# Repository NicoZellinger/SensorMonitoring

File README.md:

#Universal Data Aquisition Network System

#SensorMonitoring
In this project a system should be developed which is possible to carry out several sensor measurements and to send the values over WLAN to a central system. 
Afterwards in the central system the measuring results should be evaluated and documented for a period. 

# Hardware
In the essentials the sensor board is a WLAN module, a microcontroller and any sensor. 
The microcontroller reads the values of the sensor in a configureable frequency and transfers this to the WLAN module. 
The WLAN module sends the values to the central system (Raspberry Pi with Raspbian). 
Afterwards on the central system the measuring results are evaluated and documented. 
Beyond it, the central system administered the sensor boards. 

# Power
So that the sensor boards can be used mobile, the boards are supplied with a 3 volt battery. 
To put off the unloading of the battery as long as possible a "ultra low power" microcontroller from STMicroelectronic is used.
Besides, the controller is moved, as long as he takes up no measurement, into the Sleep mode. 
Above, the WLAN module and the sensor is separated with the help of a FET from the supply voltage (As long as no measurement is made).

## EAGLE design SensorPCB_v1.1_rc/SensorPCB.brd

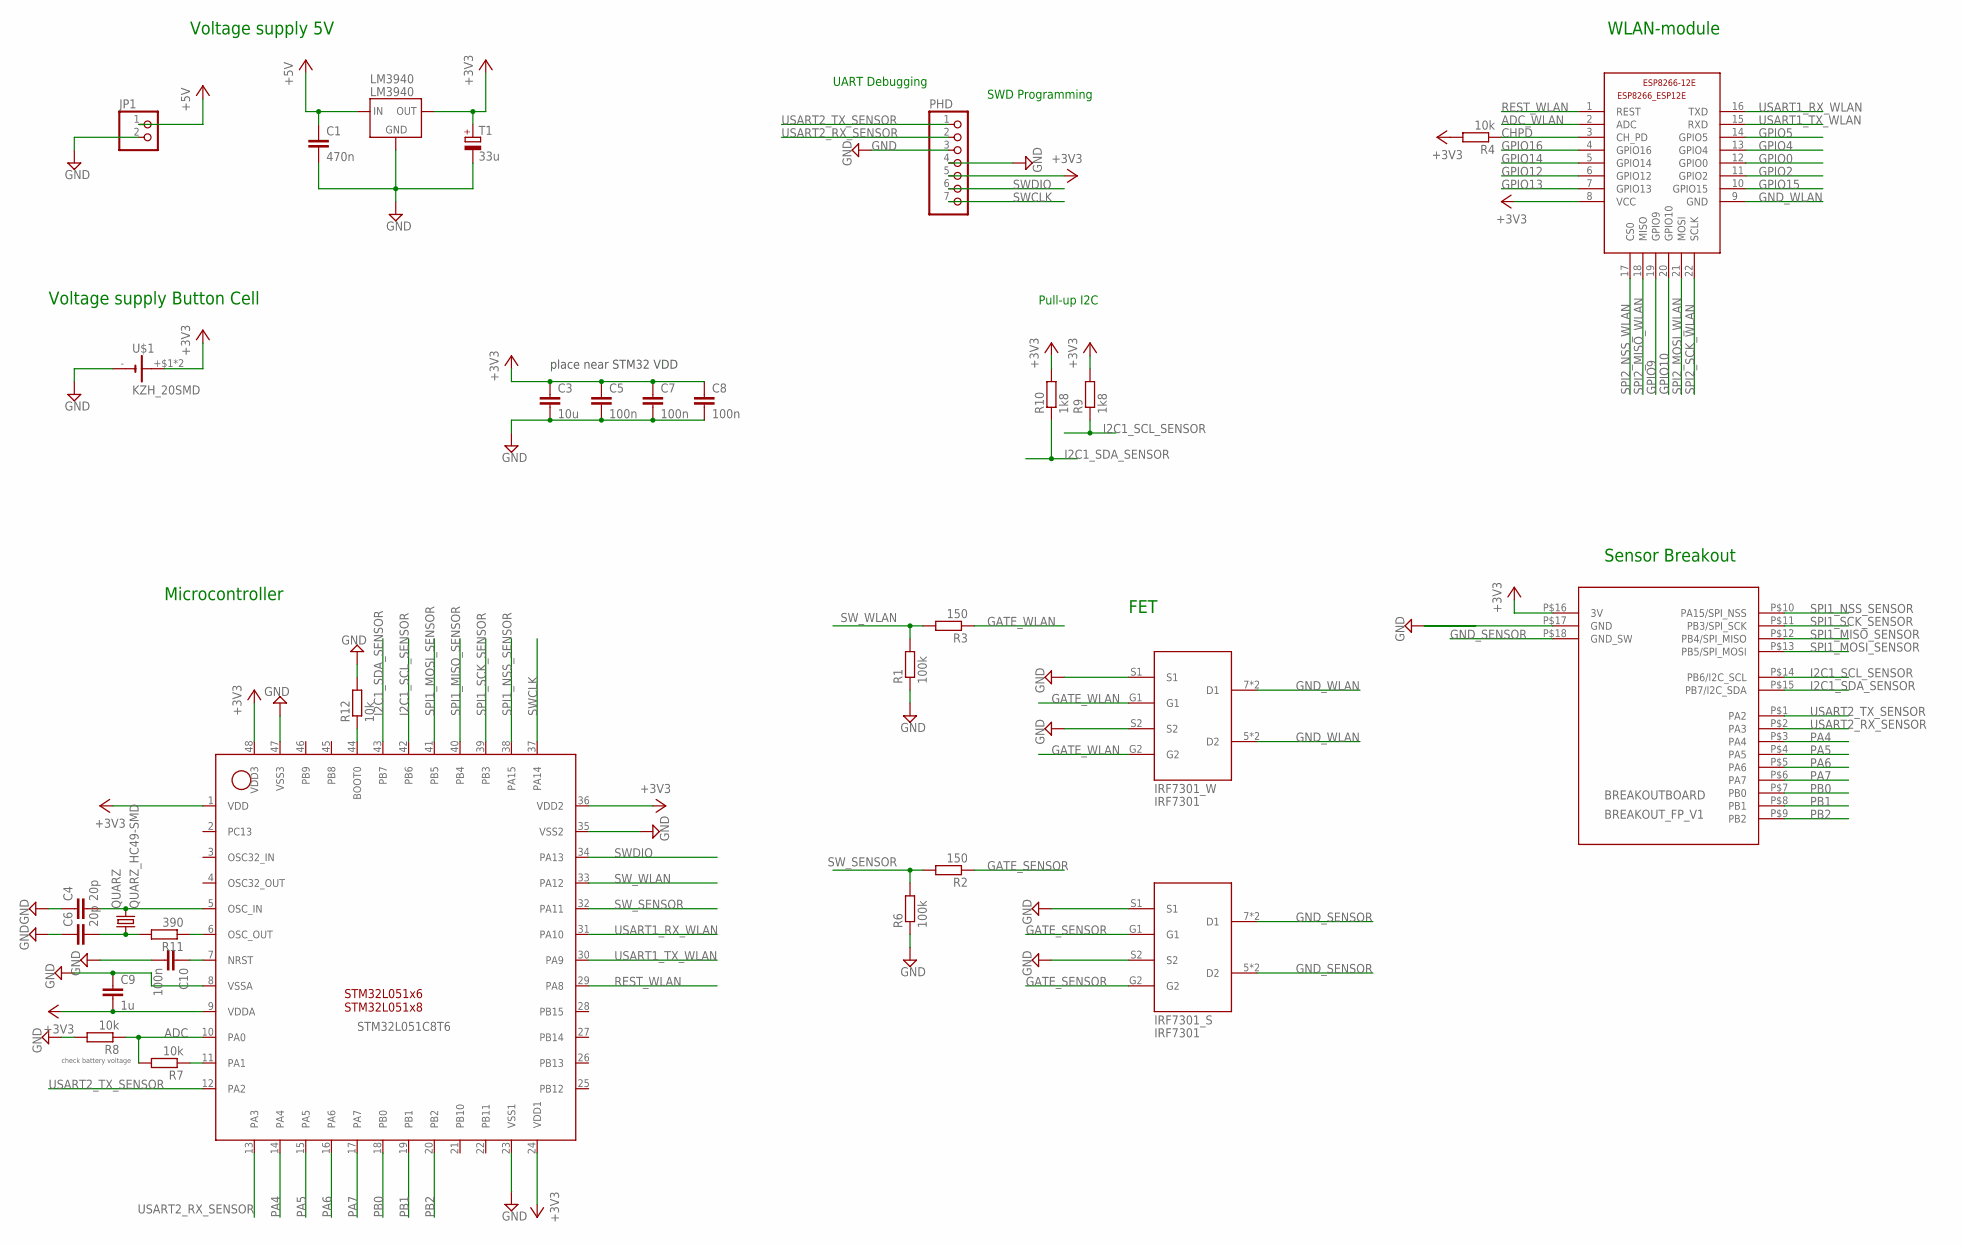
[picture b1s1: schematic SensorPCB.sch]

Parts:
BREAKOUTBOARD: BREAKOUT_FP_V1; BREAKOUT_FOOTPRINT_V1
C1: 470n; C0805
C3: 10u; C0805
C4, C6: 20p; C0805
C5, C7, C8, C10: 100n; C0805
C9: 1u; C0805
ESP8266-12E: ESP8266-12EESP8266-ESP12E; ESP8266-ESP12E
IRF7301_S, IRF7301_W: IRF7301; IRF7301_PACK_SO8
JP1: PINHD-1X2_2.54-SMD; 1X02SMD
LM3940: LM3940; LM3940_PACK
PHD: PINHD-1X7_2.54-SMD; 1X07SMD
QUARZ: QUARZ_HC49-SMD; HC49-SMD
R1, R6: 100k; R0805
R2, R3: 150; R0805
R4, R7, R8, R12: 10k; R0805
R9, R10: 1k8; R0805
R11: 390; R0805
STM32L051C8T6: STM32L051X6/8; LQFP48
T1: 33u; 1206
U$1: KZH_20SMD; KHZ_20SMD

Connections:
+3V3: BREAKOUTBOARD.P$16 (3V), C3.1, C5.1, C7.1, C8.1, C9.2, ESP8266-12E.8 (VCC), LM3940.3 (OUT), PHD.5, R4.2, R9.2, R10.2, STM32L051C8T6.1 (VDD), STM32L051C8T6.9 (VDDA), STM32L051C8T6.24 (VDD1), STM32L051C8T6.36 (VDD2), STM32L051C8T6.48 (VDD3), T1.1 (+), U$1.+$1 (+), U$1.+$2 (+)
+5V: C1.1, JP1.1, LM3940.1 (IN)
ADC: R7.2, R8.1, STM32L051C8T6.10 (PA0)
ADC_WLAN: ESP8266-12E.2 (ADC)
CHPD: ESP8266-12E.3 (CH_PD), R4.1
GATE_SENSOR: IRF7301_S.G1, IRF7301_S.G2, R2.1
GATE_WLAN: IRF7301_W.G1, IRF7301_W.G2, R3.1
GND: BREAKOUTBOARD.P$17 (GND), C1.2, C3.2, C4.1, C5.2, C6.1, C7.2, C8.2, C9.1, C10.2, IRF7301_S.S1, IRF7301_S.S2, IRF7301_W.S1, IRF7301_W.S2, JP1.2, LM3940.2 (GND), LM3940.4 (GND), PHD.3, PHD.4, R1.1, R6.1, R8.2, R12.2, STM32L051C8T6.8 (VSSA), STM32L051C8T6.23 (VSS1), STM32L051C8T6.35 (VSS2), STM32L051C8T6.47 (VSS3), T1.2 (-), U$1.-
GND_SENSOR: BREAKOUTBOARD.P$18 (GND_SW), IRF7301_S.5 (D2), IRF7301_S.7 (D1), IRF7301_S.D1, IRF7301_S.D2
GND_WLAN: ESP8266-12E.9 (GND), IRF7301_W.5 (D2), IRF7301_W.7 (D1), IRF7301_W.D1, IRF7301_W.D2
GPIO0: ESP8266-12E.12 (GPIO0)
GPIO2: ESP8266-12E.11 (GPIO2)
GPIO4: ESP8266-12E.13 (GPIO4)
GPIO5: ESP8266-12E.14 (GPIO5)
GPIO9: ESP8266-12E.19 (GPIO9)
GPIO10: ESP8266-12E.20 (GPIO10)
GPIO12: ESP8266-12E.6 (GPIO12)
GPIO13: ESP8266-12E.7 (GPIO13)
GPIO14: ESP8266-12E.5 (GPIO14)
GPIO15: ESP8266-12E.10 (GPIO15)
GPIO16: ESP8266-12E.4 (GPIO16)
I2C1_SCL_SENSOR: BREAKOUTBOARD.P$14 (PB6/I2C_SCL), R9.1, STM32L051C8T6.42 (PB6)
I2C1_SDA_SENSOR: BREAKOUTBOARD.P$15 (PB7/I2C_SDA), R10.1, STM32L051C8T6.43 (PB7)
unnamed: R7.1, STM32L051C8T6.11 (PA1)
unnamed: C6.2, QUARZ.1, R11.2
unnamed: C10.1, STM32L051C8T6.7 (NRST)
unnamed: R12.1, STM32L051C8T6.44 (BOOT0)
OSC_IN: C4.2, QUARZ.2, STM32L051C8T6.5 (OSC_IN)
OSC_OUT: R11.1, STM32L051C8T6.6 (OSC_OUT)
PA4: BREAKOUTBOARD.P$3 (PA4), STM32L051C8T6.14 (PA4)
PA5: BREAKOUTBOARD.P$4 (PA5), STM32L051C8T6.15 (PA5)
PA6: BREAKOUTBOARD.P$5 (PA6), STM32L051C8T6.16 (PA6)
PA7: BREAKOUTBOARD.P$6 (PA7), STM32L051C8T6.17 (PA7)
PB0: BREAKOUTBOARD.P$7 (PB0), STM32L051C8T6.18 (PB0)
PB1: BREAKOUTBOARD.P$8 (PB1), STM32L051C8T6.19 (PB1)
PB2: BREAKOUTBOARD.P$9 (PB2), STM32L051C8T6.20 (PB2)
REST_WLAN: ESP8266-12E.1 (REST), STM32L051C8T6.29 (PA8)
SPI1_MISO_SENSOR: BREAKOUTBOARD.P$12 (PB4/SPI_MISO), STM32L051C8T6.40 (PB4)
SPI1_MOSI_SENSOR: BREAKOUTBOARD.P$13 (PB5/SPI_MOSI), STM32L051C8T6.41 (PB5)
SPI1_NSS_SENSOR: BREAKOUTBOARD.P$10 (PA15/SPI_NSS), STM32L051C8T6.38 (PA15)
SPI1_SCK_SENSOR: BREAKOUTBOARD.P$11 (PB3/SPI_SCK), STM32L051C8T6.39 (PB3)
SPI2_MISO_WLAN: ESP8266-12E.18 (MISO)
SPI2_MOSI_WLAN: ESP8266-12E.21 (MOSI)
SPI2_NSS_WLAN: ESP8266-12E.17 (CS0)
SPI2_SCK_WLAN: ESP8266-12E.22 (SCLK)
SWCLK: PHD.7, STM32L051C8T6.37 (PA14)
SWDIO: PHD.6, STM32L051C8T6.34 (PA13)
SW_SENSOR: R2.2, R6.2, STM32L051C8T6.32 (PA11)
SW_WLAN: R1.2, R3.2, STM32L051C8T6.33 (PA12)
USART1_RX_WLAN: ESP8266-12E.16 (TXD), STM32L051C8T6.31 (PA10)
USART1_TX_WLAN: ESP8266-12E.15 (RXD), STM32L051C8T6.30 (PA9)
USART2_RX_SENSOR: BREAKOUTBOARD.P$2 (PA3), PHD.2, STM32L051C8T6.13 (PA3)
USART2_TX_SENSOR: BREAKOUTBOARD.P$1 (PA2), PHD.1, STM32L051C8T6.12 (PA2)

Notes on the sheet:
Voltage supply 5V
WLAN-module
Voltage supply Button Cell
Microcontroller
FET
Sensor Breakout
UART Debugging
SWD Programming
place near STM32 VDD
check battery voltage
Pull-up I2C

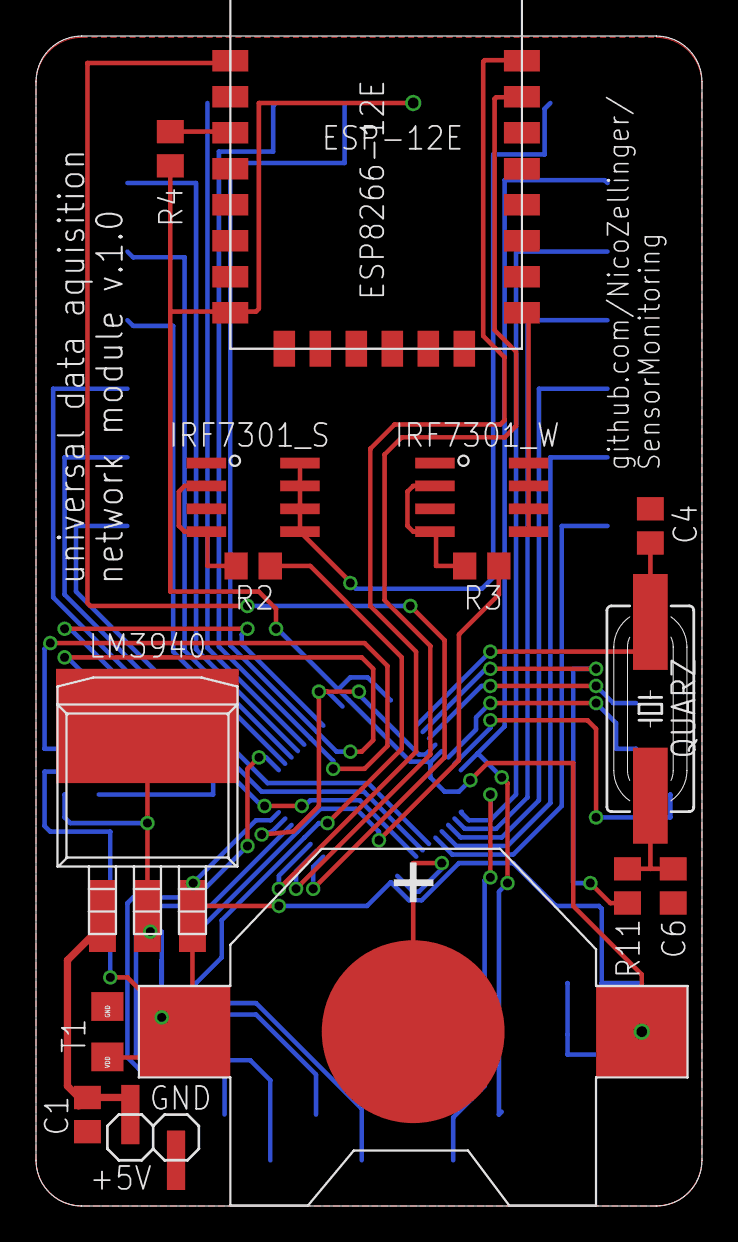
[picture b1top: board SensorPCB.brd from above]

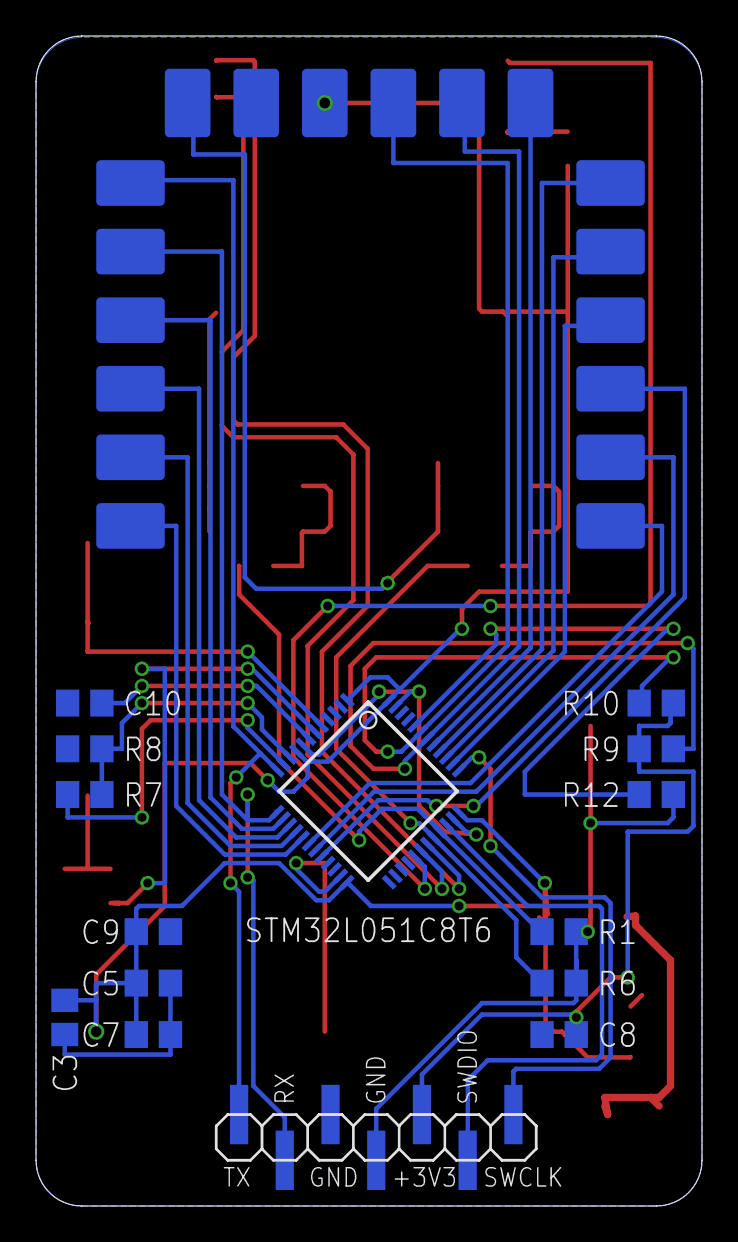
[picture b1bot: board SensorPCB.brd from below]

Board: 2 copper layers, 37.0 x 65.0 mm, 31 parts (16 on the bottom side), 37 nets.

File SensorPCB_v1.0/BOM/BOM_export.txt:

Partlist

Exported from SensorPCB.sch at 12.12.15 22:51

EAGLE Version 7.4.0 Copyright (c) 1988-2015 CadSoft

Assembly variant: 

Part          Value          Device                    Package               Library               Sheet

BREAKOUTBOARD BREAKOUT_FP_V1 BREAKOUT_FP_V1            BREAKOUT_FOOTPRINT_V1 breakout_base         1
C1            470n           C-EUC0805                 C0805                 rcl                   1
C3            10u            C-EUC0805                 C0805                 rcl                   1
C4            20p            C-EUC0805                 C0805                 rcl                   1
C5            100n           C-EUC0805                 C0805                 rcl                   1
C6            20p            C-EUC0805                 C0805                 rcl                   1
C7            100n           C-EUC0805                 C0805                 rcl                   1
C8            100n           C-EUC0805                 C0805                 rcl                   1
C9            1u             C-EUC0805                 C0805                 rcl                   1
C10           100n           C-EUC0805                 C0805                 rcl                   1
ESP8266-12E                  ESP8266-12EESP8266-ESP12E ESP8266-ESP12E        ESP8266-ESP12E        1
IRF7301_S     IRF7301        IRF7301                   IRF7301_PACK_SO8      irf7301_symb          1
IRF7301_W     IRF7301        IRF7301                   IRF7301_PACK_SO8      irf7301_symb          1
JP1                          PINHD-1X2_2.54-SMD        1X02SMD               pinhead               1
LM3940        LM3940         LM3940                    LM3940_PACK           lm3940                1
PHD                          PINHD-1X7_2.54-SMD        1X07SMD               pinhead               1
QUARZ         QUARZ_HC49-SMD QUARZ_HC49-SMD            HC49-SMD              quarz_hc49_smd        1
R1            100k           R-EU_R0805                R0805                 rcl                   1
R2            150            R-EU_R0805                R0805                 rcl                   1
R3            150            R-EU_R0805                R0805                 rcl                   1
R4            10k            R-EU_R0805                R0805                 rcl                   1
R6            100k           R-EU_R0805                R0805                 rcl                   1
R7            10k            R-EU_R0805                R0805                 rcl                   1
R8            10k            R-EU_R0805                R0805                 rcl                   1
R9            1k8            R-EU_R0805                R0805                 rcl                   1
R10           1k8            R-EU_R0805                R0805                 rcl                   1
R11           390            R-EU_R0805                R0805                 rcl                   1
R12           10k            R-EU_R0805                R0805                 rcl                   1
STM32L051C8T6 STM32L051X6/8  STM32L051X6/8             LQFP48                STM32L051x6_LQFP48XXL 1
T1            33u            CAP_TANTAL_1206           1206                  CAP_TANTAL_1206       1
U$1           KZH_20SMD      KZH_20SMD                 KHZ_20SMD             KZH_20SMD             1

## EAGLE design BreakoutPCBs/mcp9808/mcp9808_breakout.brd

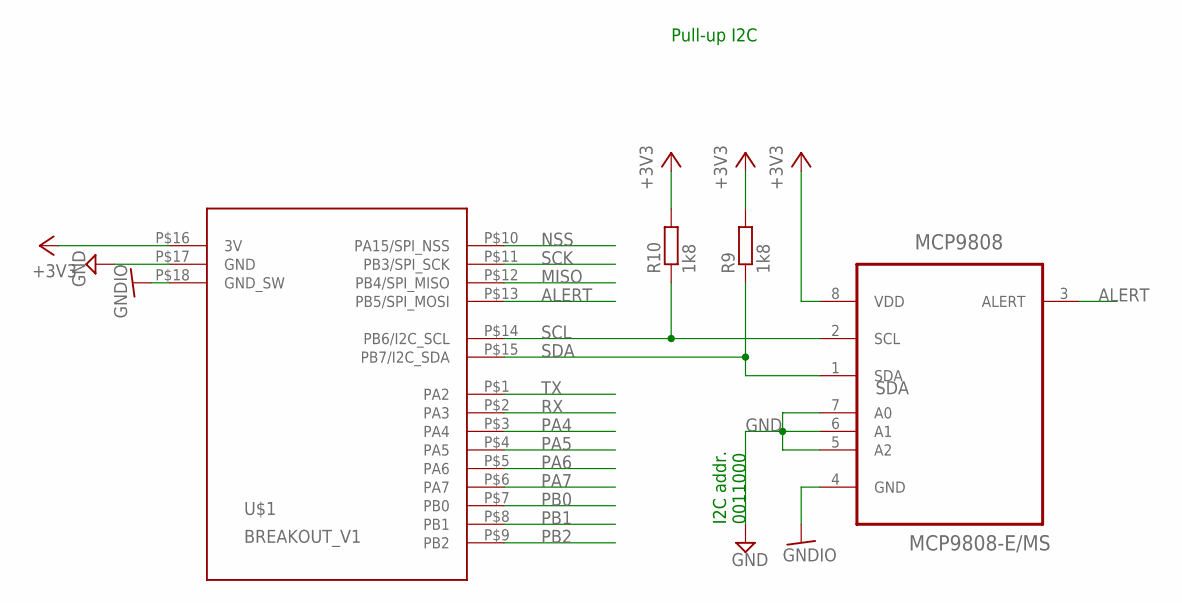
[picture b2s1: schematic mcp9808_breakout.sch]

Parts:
MCP9808: MCP9808-E/MS; SOP65P490X110-8N
R9, R10: 1k8; R0805
U$1: BREAKOUT_V1

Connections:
+3V3: MCP9808.8 (VDD), R9.2, R10.2, U$1.P$16 (3V)
ALERT: MCP9808.3 (ALERT), U$1.P$13 (PB5/SPI_MOSI)
GND: MCP9808.5 (A2), MCP9808.6 (A1), MCP9808.7 (A0), U$1.P$17 (GND)
GNDIO: MCP9808.4 (GND), U$1.P$18 (GND_SW)
MISO: U$1.P$12 (PB4/SPI_MISO)
NSS: U$1.P$10 (PA15/SPI_NSS)
PA4: U$1.P$3 (PA4)
PA5: U$1.P$4 (PA5)
PA6: U$1.P$5 (PA6)
PA7: U$1.P$6 (PA7)
PB0: U$1.P$7 (PB0)
PB1: U$1.P$8 (PB1)
PB2: U$1.P$9 (PB2)
RX: U$1.P$2 (PA3)
SCK: U$1.P$11 (PB3/SPI_SCK)
SCL: MCP9808.2 (SCL), R10.1, U$1.P$14 (PB6/I2C_SCL)
SDA: MCP9808.1 (SDA), R9.1, U$1.P$15 (PB7/I2C_SDA)
TX: U$1.P$1 (PA2)

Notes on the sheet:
I2C addr. 0011000
Pull-up I2C

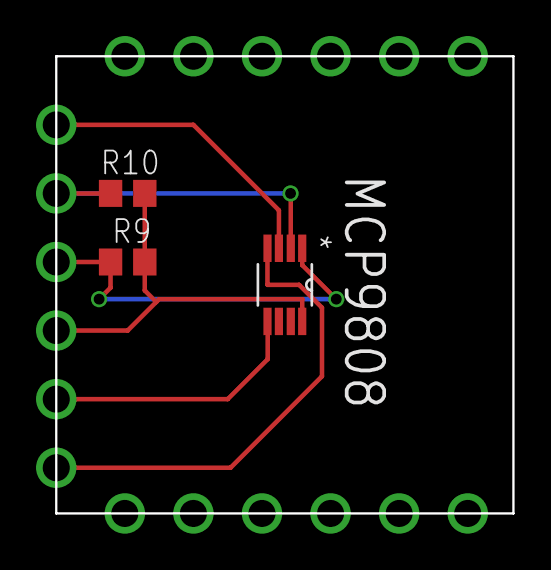
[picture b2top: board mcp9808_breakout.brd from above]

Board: 2 copper layers, 25.4 x 25.4 mm, 4 parts (0 on the bottom side), 6 nets.

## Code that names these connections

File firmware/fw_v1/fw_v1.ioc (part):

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Mcu.Name=STM32L051C(6-8)Tx
Mcu.Package=LQFP48
Mcu.UserName=STM32L051C8Tx
PA0.Mode=IN0
PA0.Signal=ADC_IN0
PA1.Signal=GPIO_Output
PA10.Mode=Asynchronous
PA10.Signal=USART1_RX
PA11.Signal=GPIO_Output
PA12.Signal=GPIO_Output
PA13.Mode=Serial_Wire
PA13.Signal=SYS_SWDIO
PA14.Mode=Serial_Wire
PA14.Signal=SYS_SWCLK
PA15.Signal=SPI1_NSS
PA2.Mode=Asynchronous
PA2.Signal=USART2_TX
PA3.Mode=Asynchronous
PA3.Signal=USART2_RX
PA8.Signal=GPIO_Output
PA9.Mode=Asynchronous
PA9.Signal=USART1_TX
PB3.Mode=Full_Duplex_Master
PB3.Signal=SPI1_SCK
PB4.Mode=Full_Duplex_Master
PB4.Signal=SPI1_MISO
PB5.Mode=Full_Duplex_Master
PB5.Signal=SPI1_MOSI
PB6.Mode=I2C
PB6.Signal=I2C1_SCL
PB7.Mode=I2C
PB7.Signal=I2C1_SDA
PH0-OSC_IN.Mode=HSE-External-Oscillator
PH0-OSC_IN.Signal=RCC_OSC_IN
PH1-OSC_OUT.Mode=HSE-External-Oscillator
PH1-OSC_OUT.Signal=RCC_OSC_OUT
RCC.HSE_VALUE=8000000
RCC.SYSCLKFreq_VALUE=32000000
RCC.SYSCLKSource=RCC_SYSCLKSOURCE_PLLCLK
board=fw_v1

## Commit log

2015-11-17 hello github
2015-11-17 schematic
2015-11-18 SensorPCB: voltage regulator footprint + wlan modul
2015-11-18 SensorPCB: FET
2015-11-20 SensorPCB: change FET + change WLAN Footprint + add MCU
2015-11-21 add quartz crystal and change mcu symbol
2015-11-23 update Schematic
2015-11-23 change FET circuit and STM32 decups
2015-11-23 add FET pull down resistor
2015-11-24 Schematic update
2015-11-24 fettes update mit Breakout board
2015-11-25 Add default Sensor + Add UART
2015-11-26 change C and R footprint from 1206 to 0805
2015-11-27 add UI design concept
2015-11-27 add first sensor breakout-7board
2015-11-27 Pinheader-Breakout: add Name of wires (tName layer)
2015-11-27 change part-name
2015-11-28 add battery
2015-11-28 some updates + add second gnd-pad for voltage regulator
2015-11-28 change STM32 footprint (tstop tcream)
2015-11-28 i2c pull up
2015-11-28 prepare layout
2015-11-28 some updates
2015-11-29 start routing
2015-11-29 routing layout beautiful but maybe not accurate
2015-11-29 update layout
2015-11-30 remote top-wires and vias from tstop layer (battery)
2015-11-30 layout update
2015-12-01 routed all signal wires, 3v and GND is absent
2015-12-01 routed all signal wires, 3v and GND are absent
2015-12-01 3v almost ready
2015-12-01 routed all 3v wires
2015-12-03 start new board version
2015-12-04 some changes
2015-12-05 routing
2015-12-05 delet temp sensor + route all signal wires
2015-12-05 routed +3v
2015-12-06 add GND
2015-12-06 edit tname and bname
2015-12-08 closed #1
2015-12-08 closed #3
2015-12-10 gerber
2015-12-10 some last improvements to get ready for version 1.0
2015-12-10 asynchron pinheader-breakout + generate gerber data
2015-12-11 update breakout pinheader
2015-12-11 update mcp breakout
2015-12-12 create gerber data + order sensorPCB, pinhead & mcp breakout
2015-12-12 Closed #4
2015-12-12 edit pics
2015-12-12 test readme update
2015-12-12 last readme update, I swear
2016-04-08 add AT command parser for ESP8266
2016-04-08 readme added for AT command parser
2016-04-08 add dev enc instuctions
2016-04-09 initial firmware
2016-05-08 fix README
